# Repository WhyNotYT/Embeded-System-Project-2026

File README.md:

# PulseRace – Competitive heart-rate monitoring

_Can you get a higher heart rate than the other guy?_

# Technical Details

We developed a shared wearable that calculates a competitive score based on heart rate and motion intensity. The technical solution utilizes an ESP32-S3, MAX30102 HR sensor, and BMI323 IMU, featuring an automated web-based registration system and cloud-synced leaderboard.

## System Overview

## Software Architecture

## Communication Diagram

## Schematic

## PCB Layout

## PCB 3D View

# Demo for Springineering Challenge

For the demo we are recreating the experience with a mobile phone, the demo code can be found under software/.

Demo Video: https://www.youtube.com/watch?v=nNgHs_067A8

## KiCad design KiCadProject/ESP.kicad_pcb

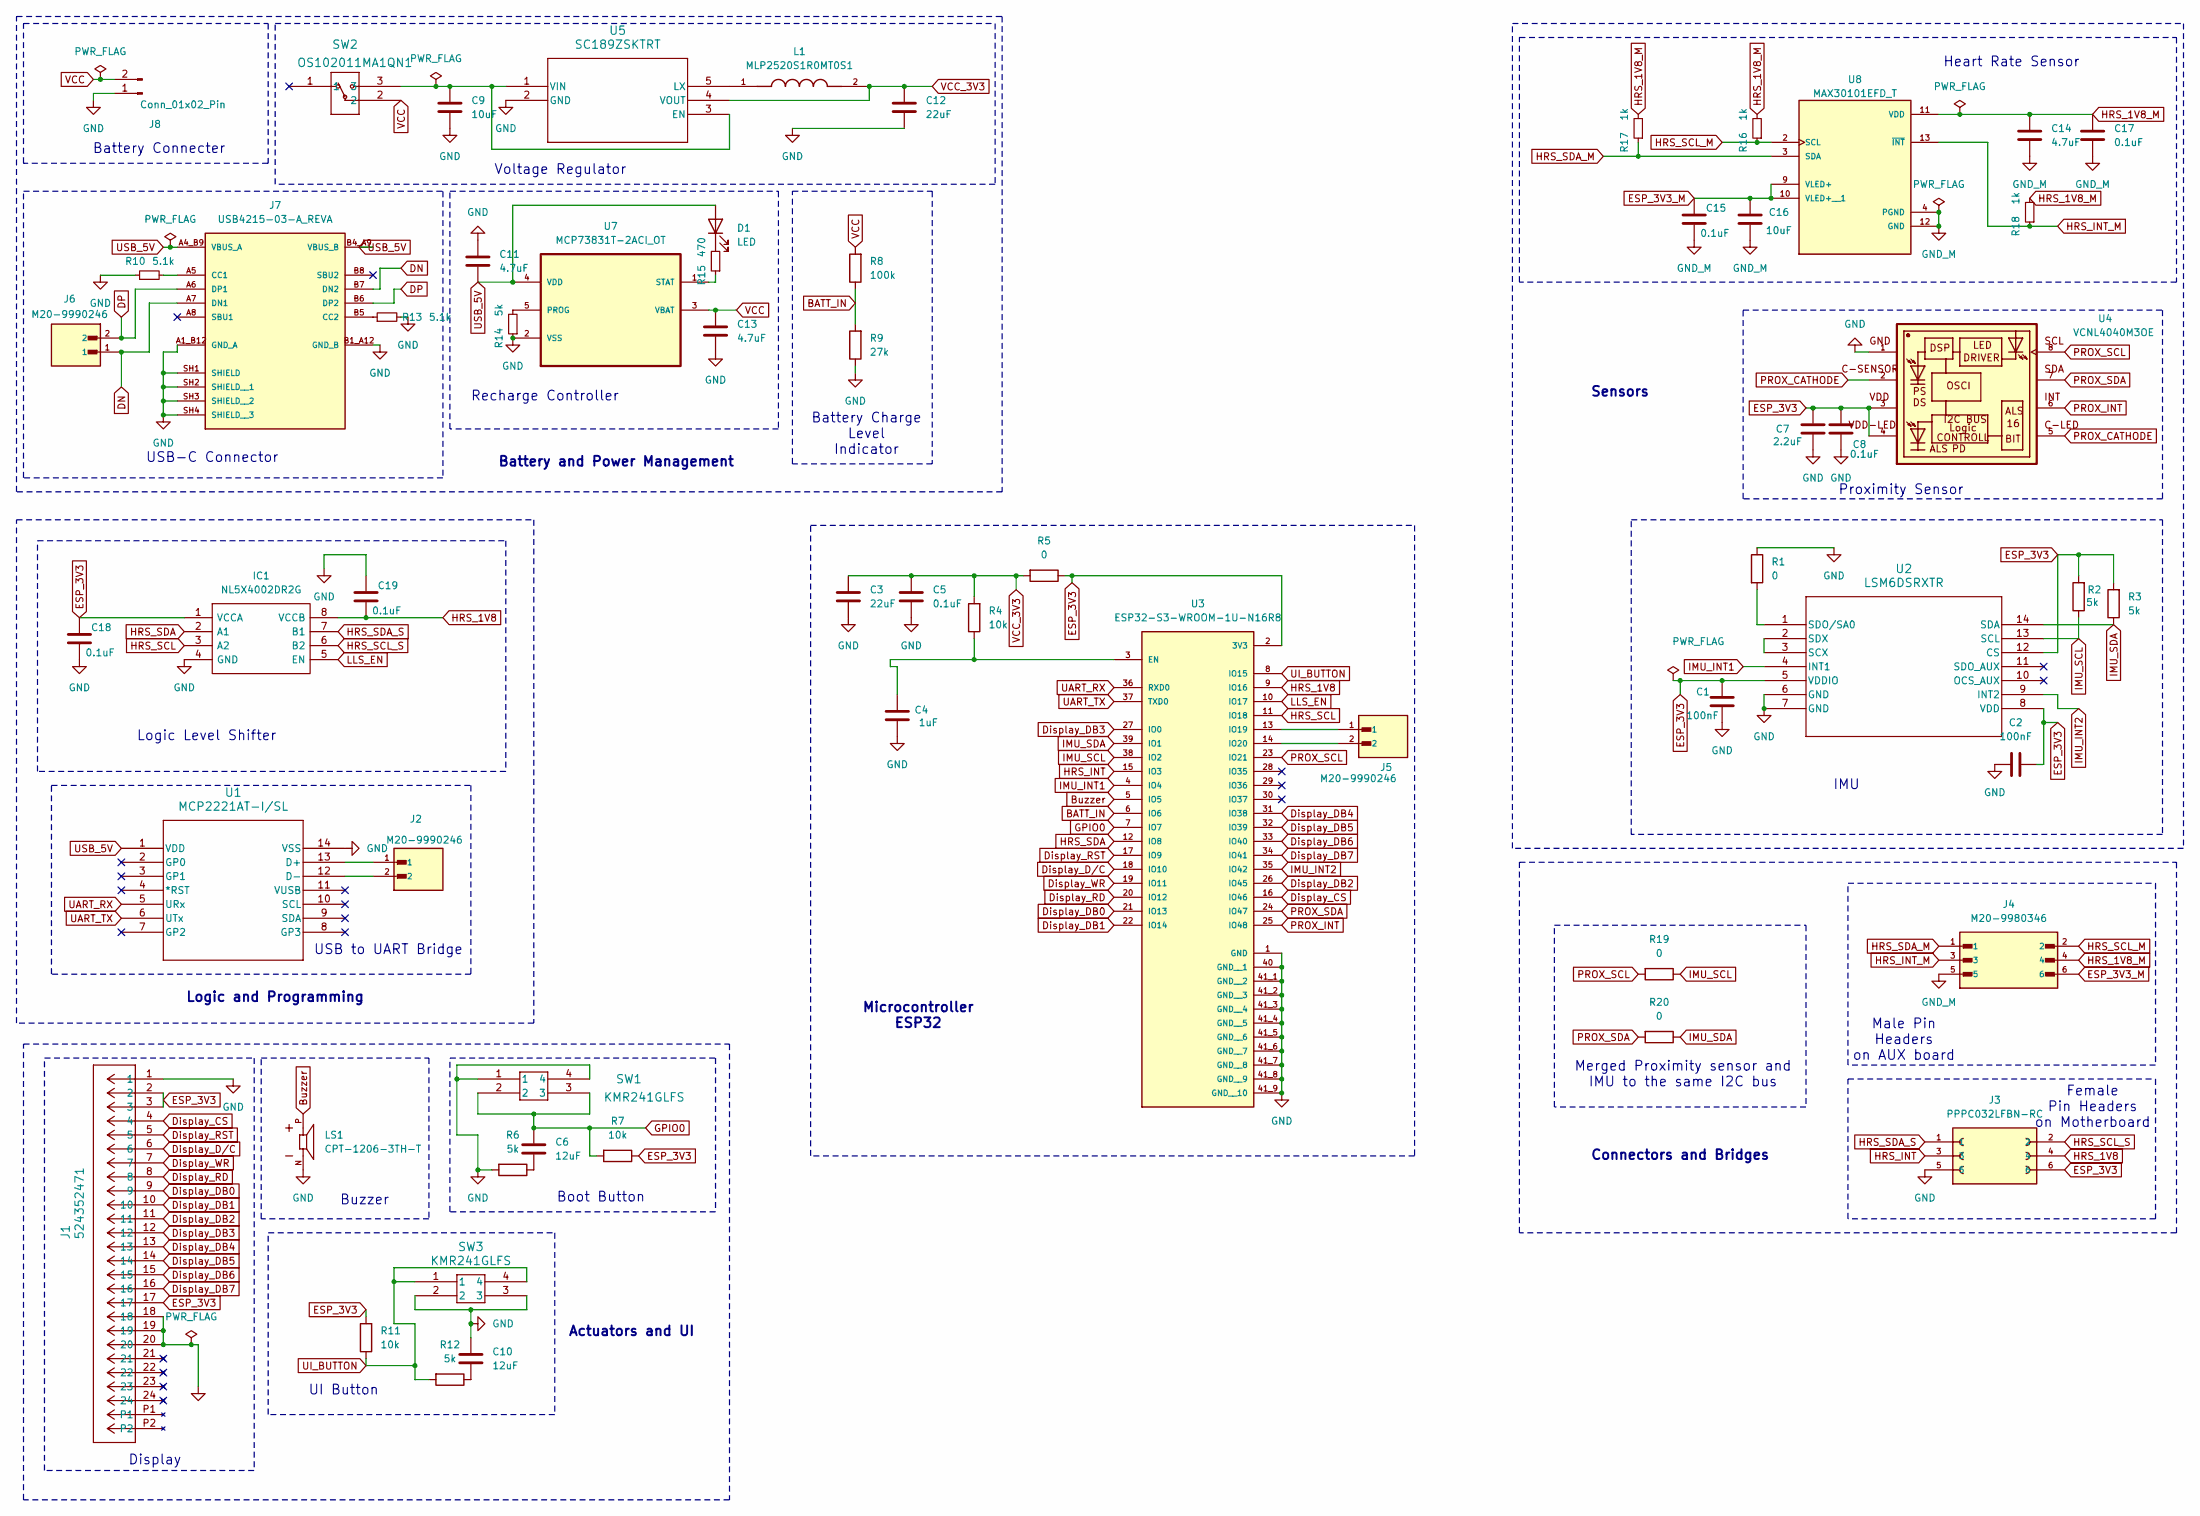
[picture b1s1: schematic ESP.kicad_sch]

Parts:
C1, C2: 100nF; C_0402_1005Metric_Pad0.74x0.62mm_HandSolder
C3, C12: 22uF; C_0402_1005Metric_Pad0.74x0.62mm_HandSolder
C4: 1uF; C_0402_1005Metric_Pad0.74x0.62mm_HandSolder
C5, C8, C15, C17, C18, C19: 0.1uF; C_0402_1005Metric_Pad0.74x0.62mm_HandSolder
C6, C10: 12uF; C_0402_1005Metric_Pad0.74x0.62mm_HandSolder
C7: 2.2uF; C_0402_1005Metric_Pad0.74x0.62mm_HandSolder
C9, C16: 10uF; C_0402_1005Metric_Pad0.74x0.62mm_HandSolder
C11, C13, C14: 4.7uF; C_0402_1005Metric_Pad0.74x0.62mm_HandSolder
D1: LED; LED_0402_1005Metric_Pad0.77x0.64mm_HandSolder
IC1: NL5X4002DR2G; SOIC127P600X175-8N; Manufacturer_Part_Number NL5X4002DR2G
J1: 524352471; CON_524352471_MOL
J2, J5, J6: M20-9990246; HARWIN_M20-9990246; PARTREV 14
J3: PPPC032LFBN-RC; SULLINS_PPPC032LFBN-RC; PARTREV L
J4: M20-9980346; HARWIN_M20-9980346
J7: USB4215-03-A_REVA; GCT_USB4215-03-A_REVA; PARTREV A
J8: Conn_01x02_Pin; PinHeader_1x02_P2.54mm_Vertical_SMD_Pin1Left
L1: MLP2520S1R0MT0S1; INDC2520X100N
LS1: CPT-1206-3TH-T; PARTREV 1.0
R1, R5, R19, R20: 0; R_0402_1005Metric
R2, R3, R6, R12: 5k; R_0402_1005Metric
R4, R7, R11: 10k; R_0402_1005Metric
R8: 100k; R_0402_1005Metric
R9: 27k; R_0402_1005Metric
R10, R13: 5.1k; R_0402_1005Metric; LCSC C105580
R14: 5k; R_0402_1005Metric; LCSC C105580
R15: 470; R_0402_1005Metric; LCSC C105580
R16, R17, R18: 1k; R_0402_1005Metric; LCSC C105580
SW1, SW3: KMR241GLFS; SWITCH_241GLFS
SW2: OS102011MA1QN1; OS102011MA1QN1_CNK
U1: MCP2221AT-I/SL; SOIC14_SL_MCH
U2: LSM6DSRXTR; LGA-14L_STM-L
U3: ESP32-S3-WROOM-1U-N16R8; XCVR_ESP32-S3-WROOM-1U-N16R8; PARTREV v1.1
U4: VCNL4040M3OE; VISHAY_VCNL4040_4X2X1.1
U5: SC189ZSKTRT; SOT23-5-SC189_SEM
U7: MCP73831T-2ACI_OT; MPN MCP73831T-2ACI/OT
U8: MAX30101EFD_T; PSON80P560X330X165-14N; PARTREV 2

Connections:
BATT_IN: R8.1, R9.2, U3.6 (IO6)
Buzzer: LS1.P, U3.5 (IO5)
DN: J6.1, J7.A7 (DN1), J7.B7 (DN2)
DP: J6.2, J7.A6 (DP1), J7.B6 (DP2)
Display_CS: J1.4, U3.16 (IO46)
Display_DB0: J1.9, U3.21 (IO13)
Display_DB1: J1.10, U3.22 (IO14)
Display_DB2: J1.11, U3.26 (IO45)
Display_DB3: J1.12, U3.27 (IO0)
Display_DB4: J1.13, U3.31 (IO38)
Display_DB5: J1.14, U3.32 (IO39)
Display_DB6: J1.15, U3.33 (IO40)
Display_DB7: J1.16, U3.34 (IO41)
Display_D/C: J1.6, U3.18 (IO10)
Display_RD: J1.8, U3.20 (IO12)
Display_RST: J1.5, U3.17 (IO9)
Display_WR: J1.7, U3.19 (IO11)
ESP_3V3: C1.1, C2.1, C7.1, C8.1, C18.1, IC1.1 (VCCA), J1.2, J1.3, J1.17, J3.6, R2.2, R3.2, R5.1, R7.1, R11.2, U2.5 (VDDIO), U2.8 (VDD), U2.12 (CS), U3.2 (3V3), U4.3, U4.4
ESP_3V3_M: C15.1, C16.1, J4.6, U8.9 (VLED+), U8.10 (VLED+__1)
GND: C1.2, C2.2, C3.2, C4.1, C5.2, C7.2, C8.2, C9.1, C10.2, C11.2, C12.1, C13.1, C18.2, C19.1, IC1.4 (GND), J1.1, J1.18, J1.19, J1.20, J3.5, J7.A1_B12 (GND_A), J7.B1_A12 (GND_B), J7.SH1 (SHIELD), J7.SH2 (SHIELD__1), J7.SH3 (SHIELD__2), J7.SH4 (SHIELD__3), J8.1, LS1.N, R1.1, R6.2, R9.1, R10.1, R13.2, R14.1, SW1.1, SW1.4, SW3.2, SW3.3, U1.14 (VSS), U2.6 (GND), U2.7 (GND), U3.1 (GND), U3.40 (GND__1), U3.41_1 (GND__2), U3.41_2 (GND__3), U3.41_3 (GND__4), U3.41_4 (GND__5), U3.41_5 (GND__6), U3.41_6 (GND__7), U3.41_7 (GND__8), U3.41_8 (GND__9), U3.41_9 (GND__10), U4.1, U5.2 (GND), U7.2 (VSS)
GND_M: C14.2, C15.2, C16.2, C17.2, J4.5, U8.4 (PGND), U8.12 (GND)
GPIO0: C6.2, R7.2, SW1.2, SW1.3, U3.7 (IO7)
HRS_1V8: C19.2, IC1.8 (VCCB), J3.4, U3.9 (IO16)
HRS_1V8_M: C14.1, C17.1, J4.4, R16.2, R17.2, R18.2, U8.11 (VDD)
HRS_INT: J3.3, U3.15 (IO3)
HRS_INT_M: J4.3, R18.1, U8.13 (~INT)
HRS_SCL: IC1.3 (A2), U3.11 (IO18)
HRS_SCL_M: J4.2, R16.1, U8.2 (SCL)
HRS_SCL_S: IC1.6 (B2), J3.2
HRS_SDA: IC1.2 (A1), U3.12 (IO8)
HRS_SDA_M: J4.1, R17.1, U8.3 (SDA)
HRS_SDA_S: IC1.7 (B1), J3.1
IMU_INT1: U2.4 (INT1), U3.4 (IO4)
IMU_INT2: U2.9 (INT2), U3.35 (IO42)
IMU_SCL: R2.1, R19.1, U2.13 (SCL), U3.38 (IO2)
IMU_SDA: R3.1, R20.1, U2.14 (SDA), U3.39 (IO1)
LLS_EN: IC1.5 (EN), U3.10 (IO17)
unnamed: C6.1, R6.1
unnamed: C10.1, R12.1
unnamed: D1.1 (K), R15.2
unnamed: J7.A5 (CC1), R10.2
unnamed: J7.B5 (CC2), R13.1
unnamed: J2.1, U1.13 (D+)
unnamed: J2.2, U1.12 (D-)
unnamed: U2.2 (SDX), U2.3 (SCX)
unnamed: R1.2, U2.1 (SDO/SA0)
unnamed: C4.2, R4.1, U3.3 (EN)
unnamed: J5.1, U3.13 (IO19)
unnamed: J5.2, U3.14 (IO20)
unnamed: C9.2, SW2.3, U5.1 (VIN), U5.3 (EN)
unnamed: L1.1, U5.5 (LX)
unnamed: R14.2, U7.5 (PROG)
unnamed: R15.1, U7.1 (STAT)
PROX_CATHODE: U4.2, U4.5
PROX_INT: U3.25 (IO48), U4.6
PROX_SCL: R19.2, U3.23 (IO21), U4.8
PROX_SDA: R20.2, U3.24 (IO47), U4.7
UART_RX: U1.5 (URx), U3.36 (RXD0)
UART_TX: U1.6 (UTx), U3.37 (TXD0)
UI_BUTTON: R11.1, R12.2, SW3.1, SW3.4, U3.8 (IO15)
USB_5V: C11.1, D1.2 (A), J7.A4_B9 (VBUS_A), J7.B4_A9 (VBUS_B), U1.1 (VDD), U7.4 (VDD)
VCC: C13.2, J8.2, R8.2, SW2.2, U7.3 (VBAT)
VCC_3V3: C3.1, C5.1, C12.2, L1.2, R4.2, R5.2, U5.4 (VOUT)

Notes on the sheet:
Recharge Controller
Sensors
Battery Connecter
Voltage Regulator
Connectors and Bridges
Actuators and UI
Male Pin Headers on AUX board
Display
Microcontroller ESP32
USB to UART Bridge
Female Pin Headers on Motherboard
Buzzer
Proximity Sensor
Logic Level Shifter
Logic and Programming
UI Button
Boot Button
Heart Rate Sensor
IMU
Battery Charge Level Indicator
USB-C Connector
Merged Proximity sensor and IMU to the same I2C bus
Battery and Power Management

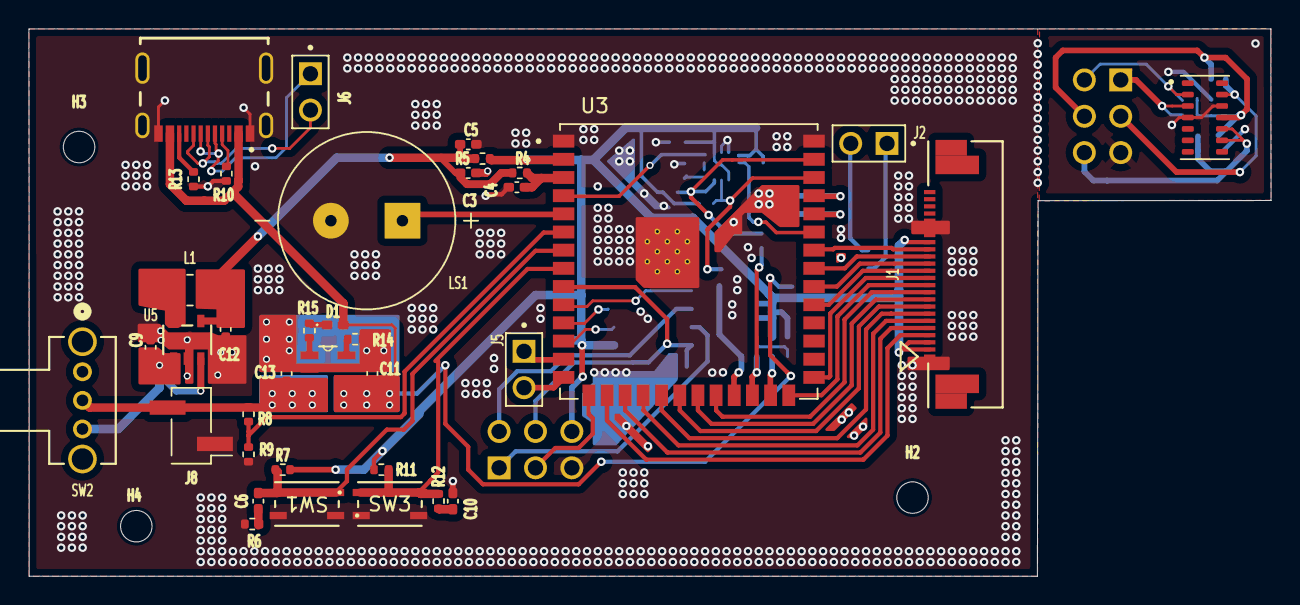
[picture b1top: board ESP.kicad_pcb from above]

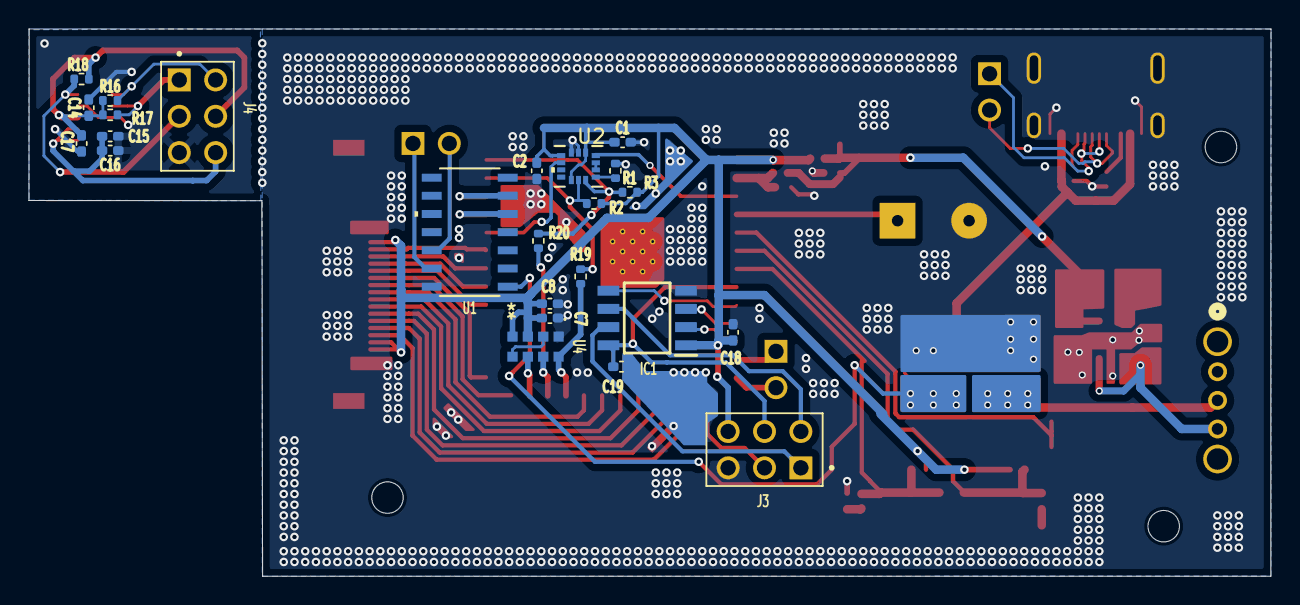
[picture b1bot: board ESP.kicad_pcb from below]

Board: 2 copper layers, 86.8 x 38.3 mm, 64 parts (24 on the bottom side), 63 nets.

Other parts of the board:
H2, H3, H4: MountingHole; MountingHole_2.2mm_M2

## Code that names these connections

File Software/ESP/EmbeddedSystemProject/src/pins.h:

#pragma once

// ── Display (8-bit parallel) ──────────────────────────────────────────────────
#define PIN_DISP_DB0 17
#define PIN_DISP_DB1 38
#define PIN_DISP_DB2 39
#define PIN_DISP_DB3 40
#define PIN_DISP_DB4 41
#define PIN_DISP_DB5 42
#define PIN_DISP_DB6 2
#define PIN_DISP_DB7 1
#define PIN_DISP_CS 5
#define PIN_DISP_RST 6
#define PIN_DISP_DC 7 // D/C  (RS in datasheet)
#define PIN_DISP_WR 15
#define PIN_DISP_RD 16

// ── Heart Rate Sensor (MAX30101) ─────────────────────────────────────────────
// Sits behind a logic-level-shifter; I2C address 0x57
#define PIN_HRS_SDA 9
#define PIN_HRS_SCL 10
#define PIN_HRS_INT 12
#define PIN_LLS_EN 11 // Logic-level-shifter enable (active HIGH)
#define PIN_HRS_18V 8 // PWM-filtered 1.8 V reference output
// IO8 = HRS_1.8V reference – driven via ledc in main.cpp

// ── Proximity Sensor (VCNL4040) ──────────────────────────────────────────────
// I2C address 0x60
#define PIN_PROX_SDA 44
#define PIN_PROX_SCL 43
#define PIN_PROX_INT 14

// ── IMU (LSM6DSRX) ───────────────────────────────────────────────────────────
#define PIN_IMU_SDA 48
#define PIN_IMU_SCL 45
// #define PIN_IMU_INT 47

// ── Misc ─────────────────────────────────────────────────────────────────────
#define PIN_UI_BUTTON 3
#define PIN_BATT_IN 4 // ADC input for battery voltage divider
#define PIN_BUZZER 18
#define PIN_BOOT_BTN 46 // GPIO0 / boot button

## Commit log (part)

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2026-04-12 Updates for Springineering
2026-04-12 Final Updates
